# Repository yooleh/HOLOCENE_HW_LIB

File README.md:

# HOLOCENE_HW_LIB
Footprints and Symbols

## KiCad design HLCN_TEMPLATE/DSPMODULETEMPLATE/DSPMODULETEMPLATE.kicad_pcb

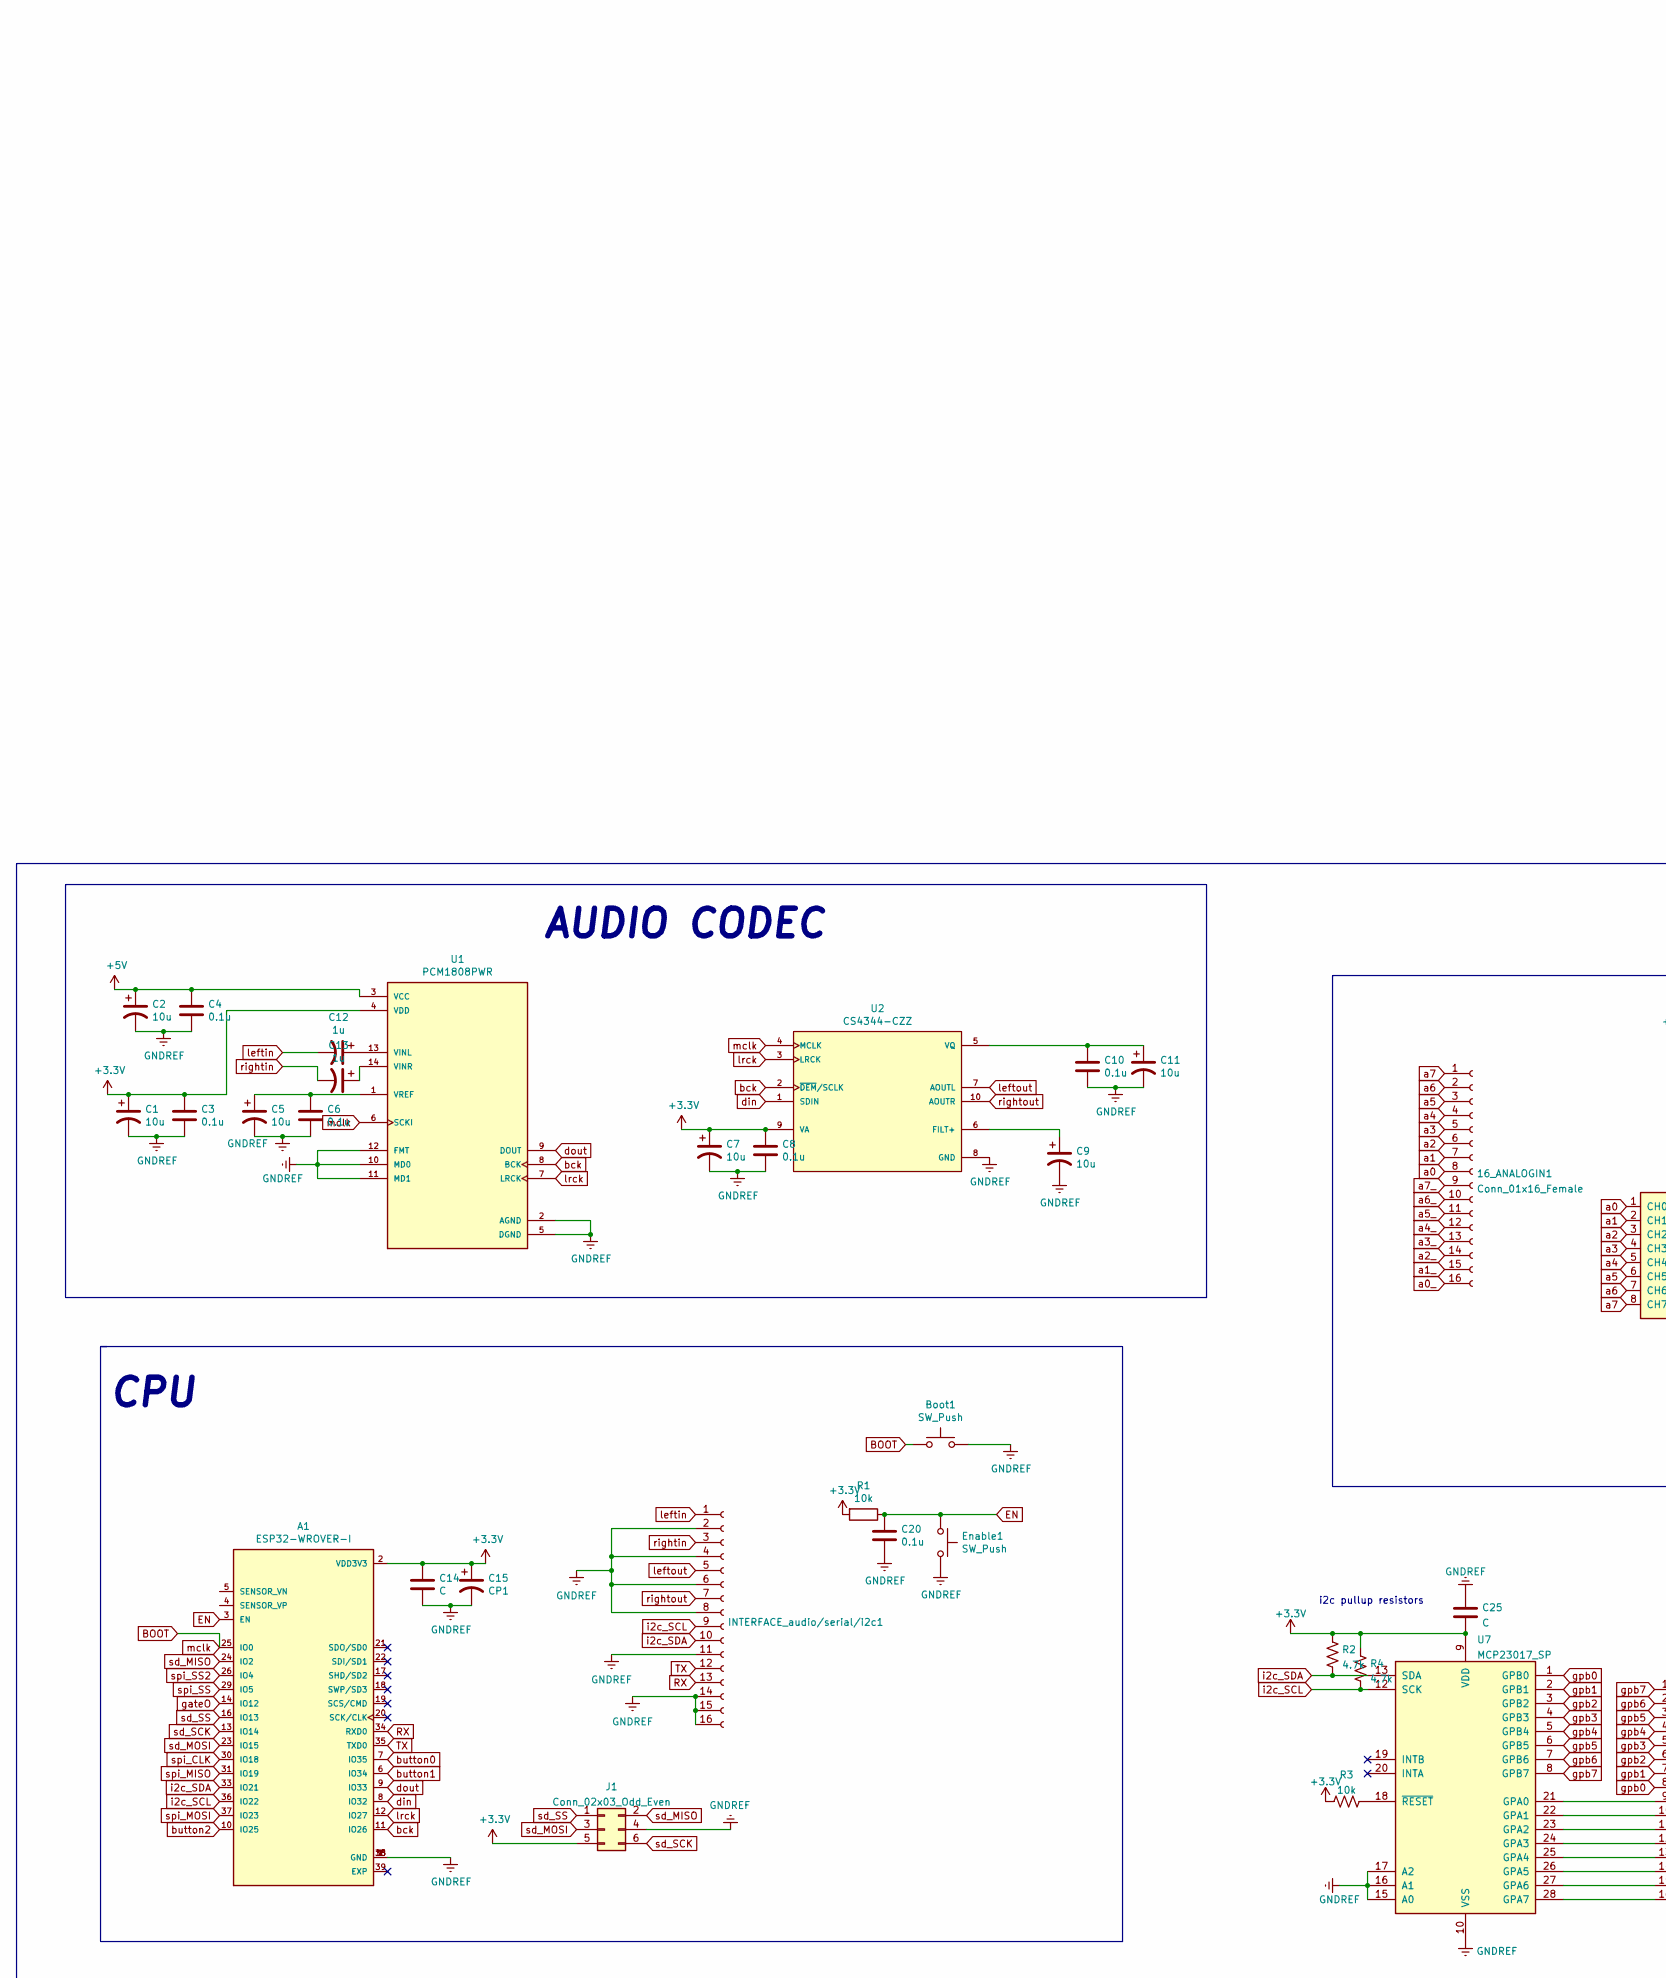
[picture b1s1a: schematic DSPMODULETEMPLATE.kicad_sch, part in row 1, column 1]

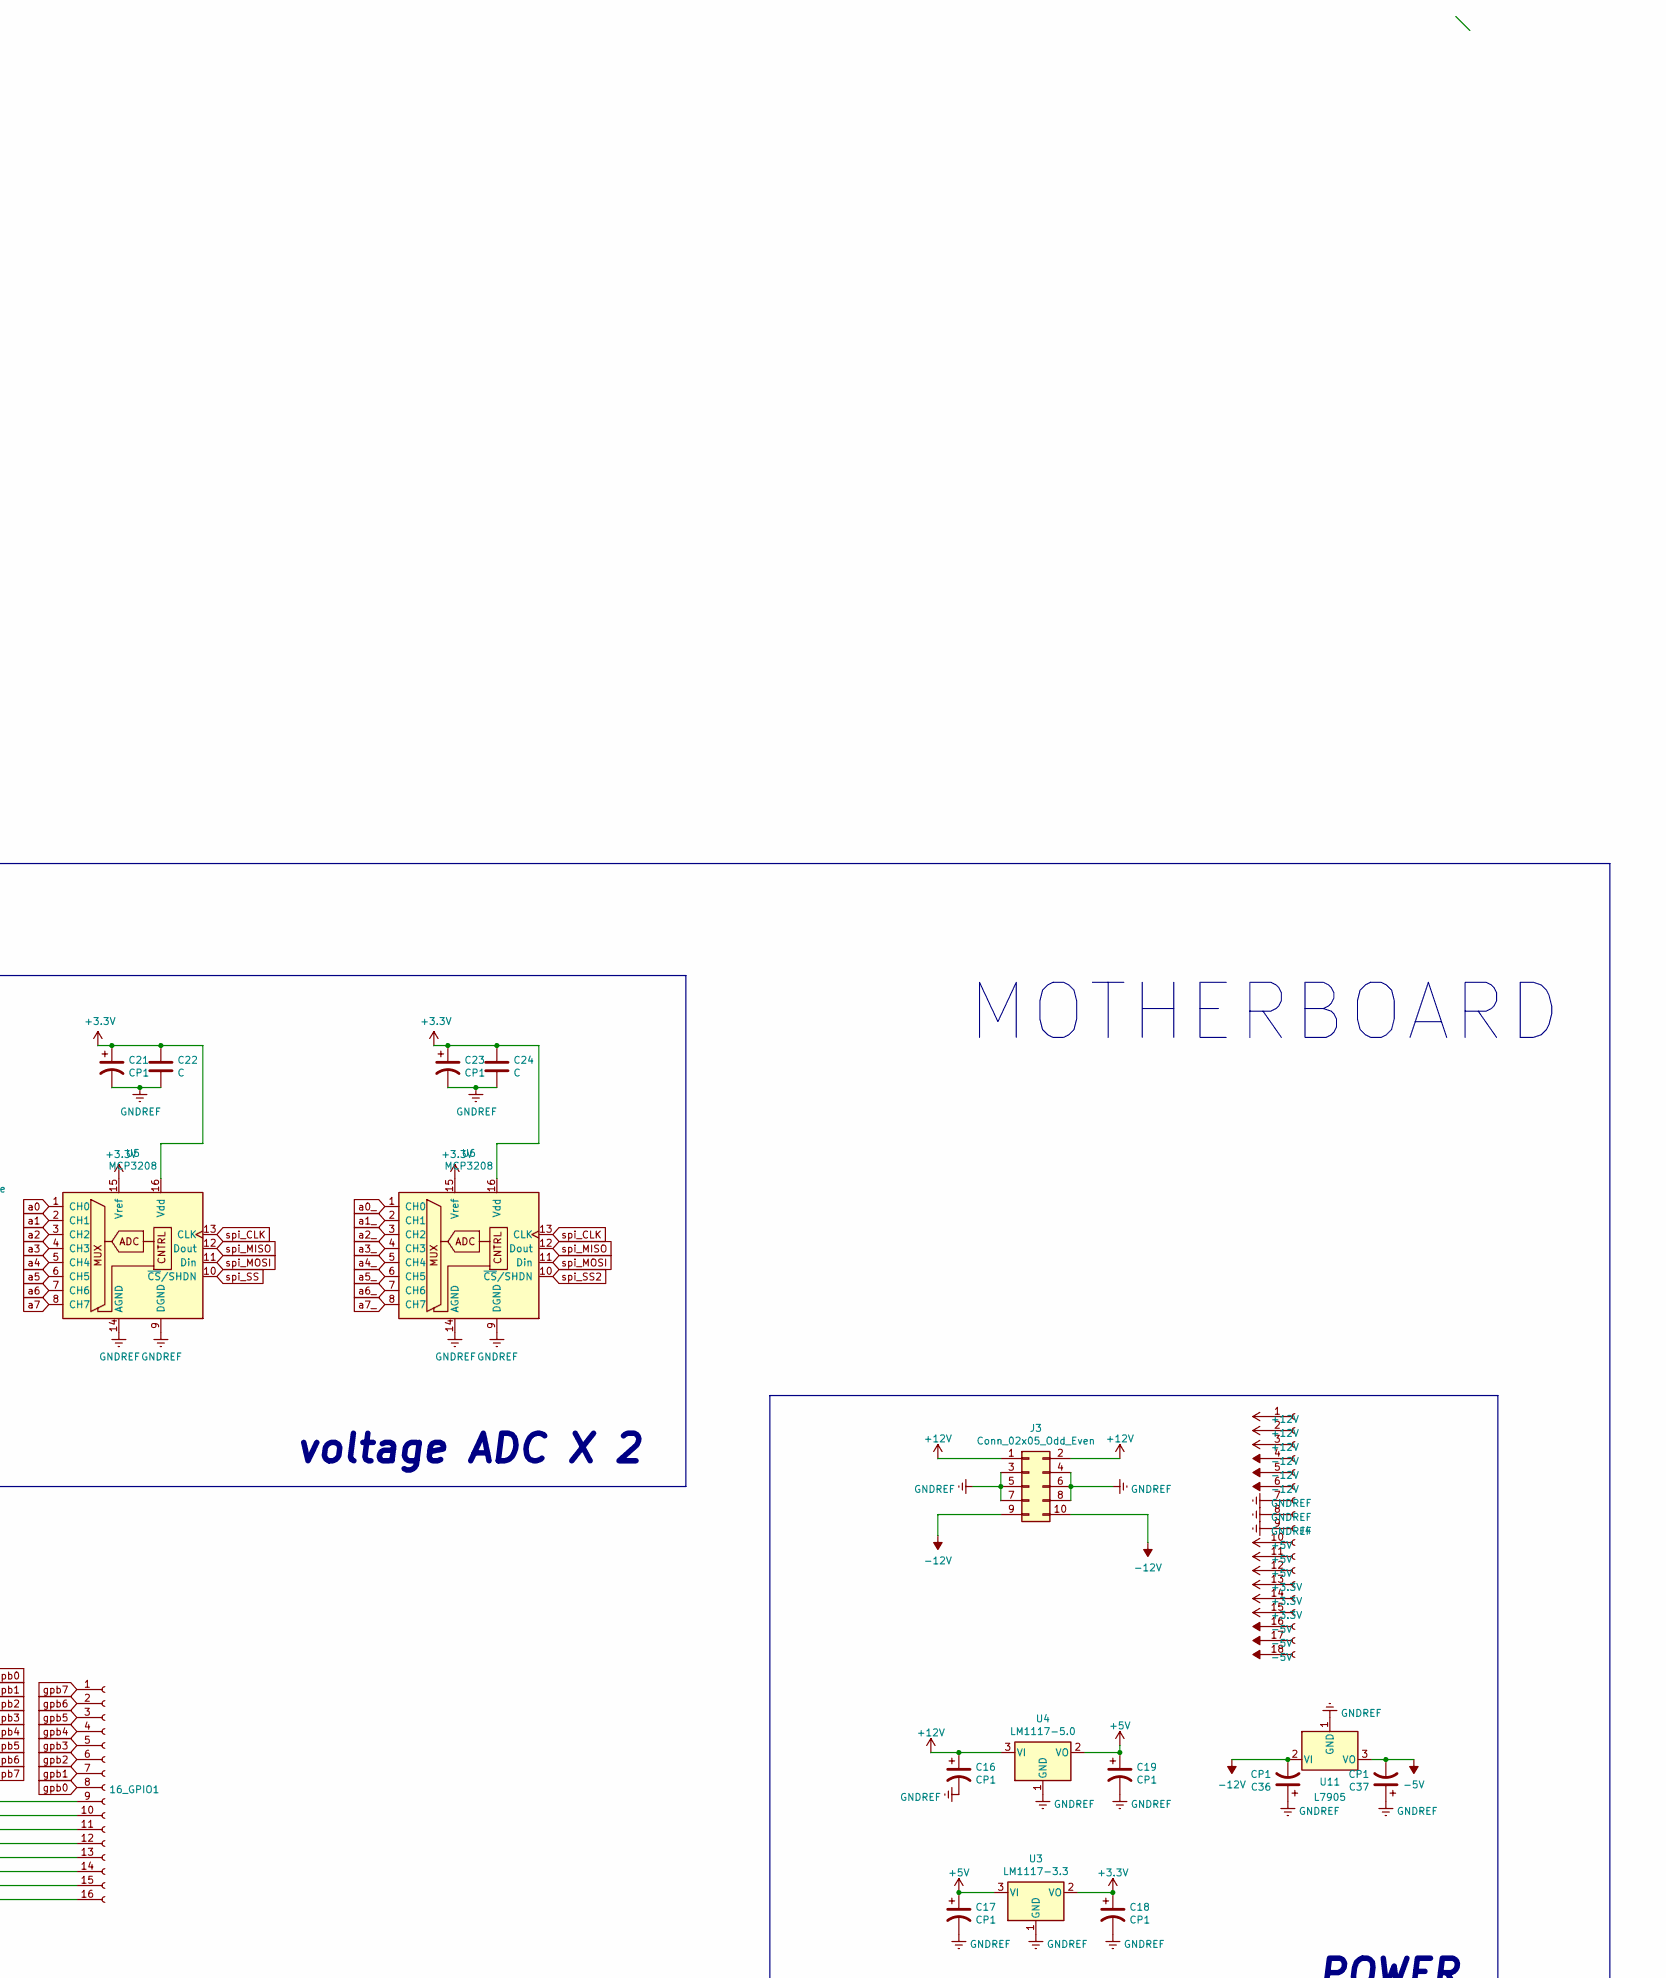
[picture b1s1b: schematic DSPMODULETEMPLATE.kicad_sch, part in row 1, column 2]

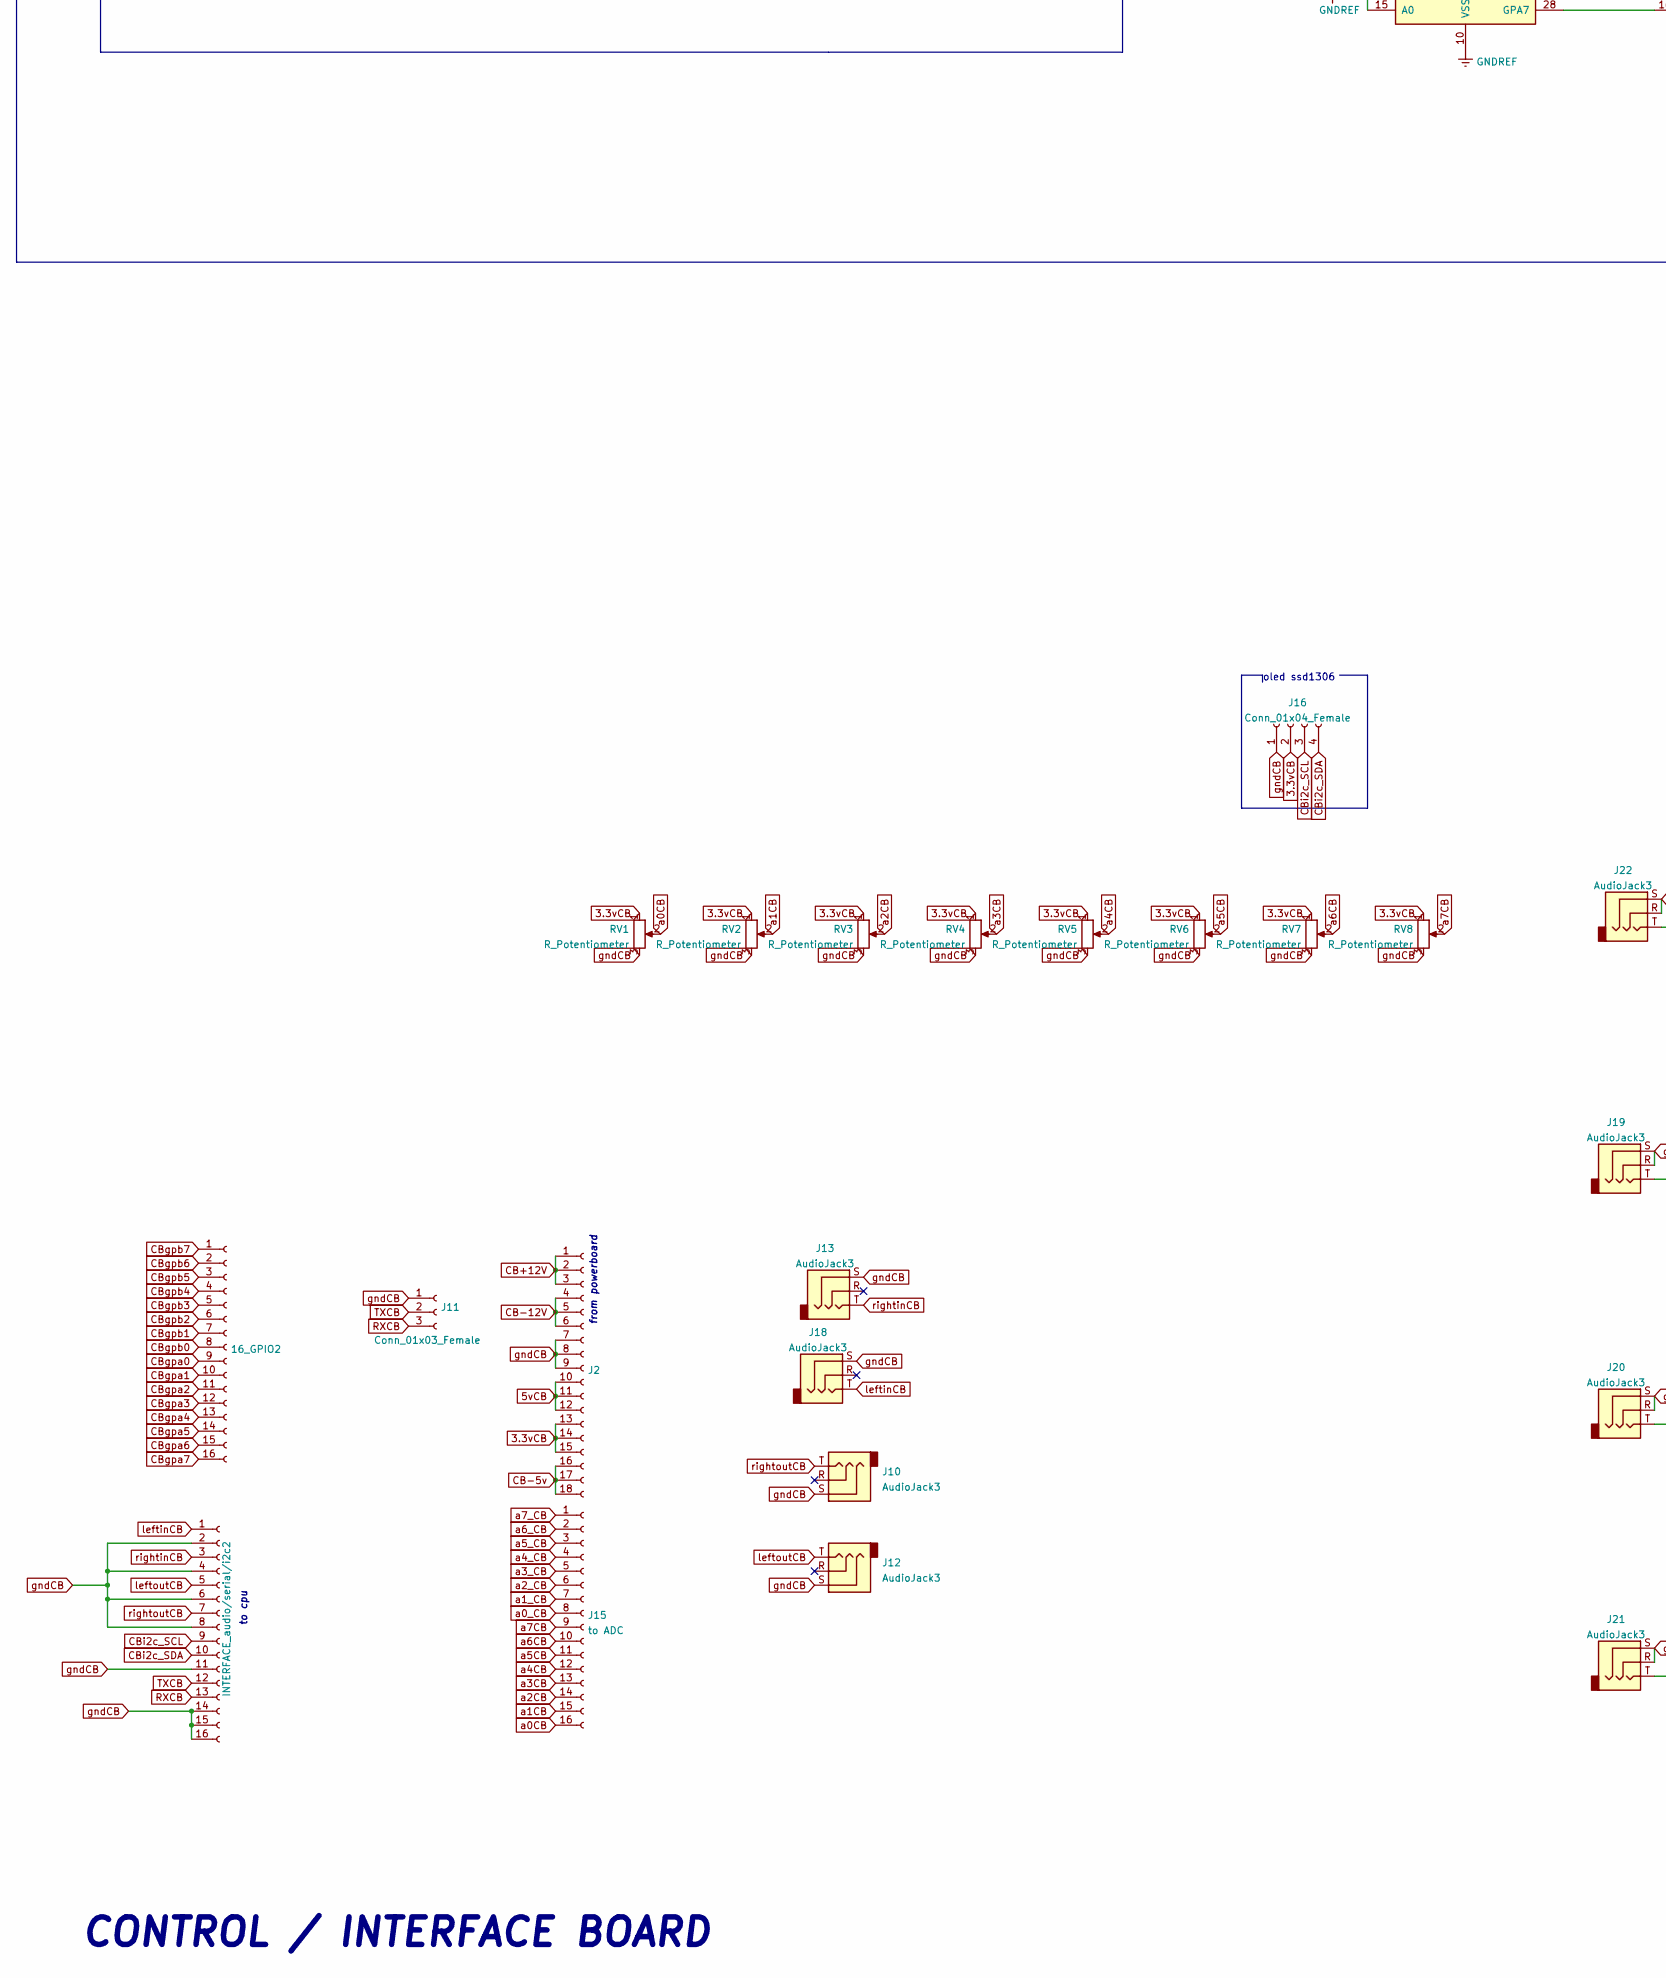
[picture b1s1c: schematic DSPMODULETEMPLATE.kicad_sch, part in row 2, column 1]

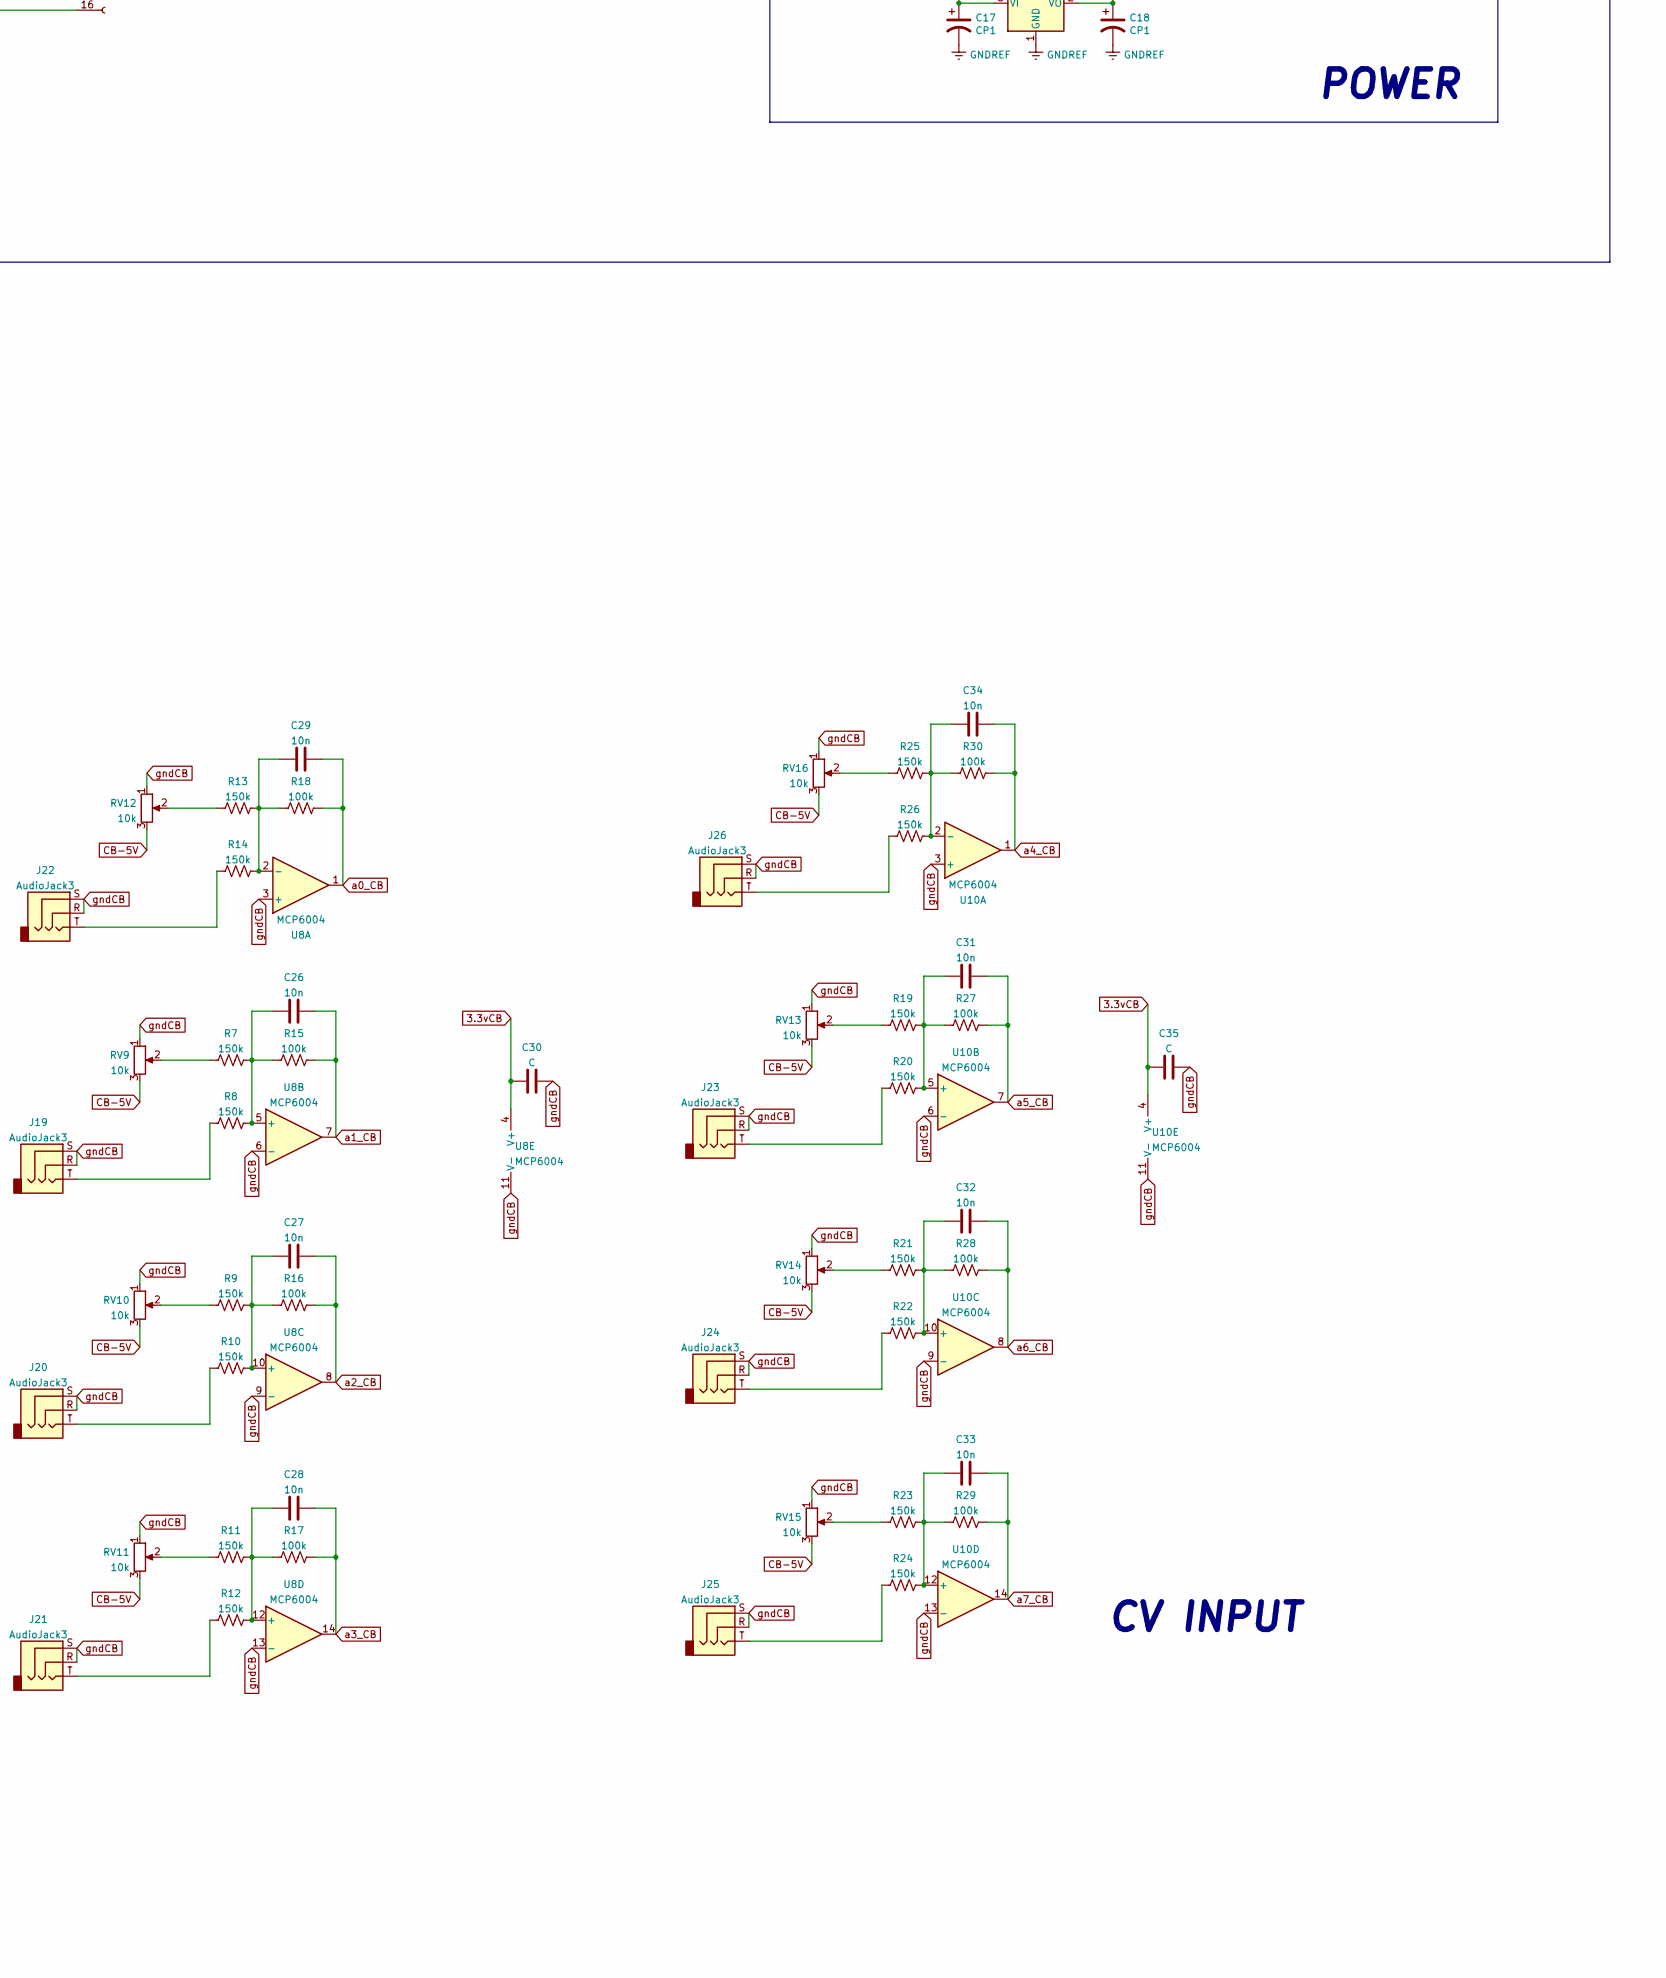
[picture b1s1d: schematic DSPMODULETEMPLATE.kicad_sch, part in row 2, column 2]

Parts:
16_ANALOGIN1, 16_GPIO1, 16_GPIO2: Conn_01x16_Female; PinSocket_1x16_P2.54mm_Vertical
A1: ESP32-WROVER-I; ESP32-WROVER
Boot1: SW_Push; SW_Push_SPST_NO_Alps_SKRK
C1, C2, C5, C7, C9, C11: 10u; CP_Elec_4x5.3
C3, C4, C6, C8, C10, C20: 0.1u; C_0805_2012Metric_Pad1.18x1.45mm_HandSolder
C12, C13: 1u; CP_Elec_4x5.3
C14, C22, C24, C25, C30, C35: C; C_0805_2012Metric_Pad1.18x1.45mm_HandSolder
C15, C16, C17, C18, C19, C21, C23, C36, C37: CP1; CP_Elec_4x5.3
C26, C27, C28, C29, C31, C32, C33, C34: 10n; C_0805_2012Metric_Pad1.18x1.45mm_HandSolder
Enable1: SW_Push; SW_Push_SPST_NO_Alps_SKRK
INTERFACE_audio/serial/i2c1, INTERFACE_audio/serial/i2c2: Conn_01x16_Female; PinHeader_1x16_P2.54mm_Vertical
J1: Conn_02x03_Odd_Even; PinHeader_2x03_P2.54mm_Vertical
J2, J4: Conn_01x18_Female; PinHeader_1x18_P2.54mm_Vertical
J3: Conn_02x05_Odd_Even; PinHeader_2x05_P2.54mm_Vertical
J10, J12, J13, J18, J19, J20, J21, J22, J23, J24, J25, J26: AudioJack3; AudioJack_3.5mm
J11: Conn_01x03_Female; PinHeader_1x03_P2.54mm_Vertical
J15: to ADC; PinSocket_1x16_P2.54mm_Vertical
J16: Conn_01x04_Female; SSD1306
R1, R3: 10k; R_0805_2012Metric_Pad1.20x1.40mm_HandSolder
R2, R4: 4.7k; R_0805_2012Metric_Pad1.20x1.40mm_HandSolder
R7, R8, R9, R10, R11, R12, R13, R14, R19, R20, R21, R22, R23, R24, R25, R26: 150k; R_0805_2012Metric_Pad1.20x1.40mm_HandSolder
R15, R16, R17, R18, R27, R28, R29, R30: 100k; R_0805_2012Metric_Pad1.20x1.40mm_HandSolder
RV1, RV2, RV3, RV4, RV6, RV8: R_Potentiometer; Potentiometer_Alps_RK09K_Single_Vertical
RV5, RV7: R_Potentiometer; Potentiometer_Bourns_PTA4543_Single_Slide
RV9, RV10, RV11, RV12, RV13, RV14, RV15, RV16: 10k; Potentiometer_Alps_RK09K_Single_Vertical
U1: PCM1808PWR; TSSOP-14_4.4x5mm_P0.65mm
U2: CS4344-CZZ; TSSOP-10_3x3mm_P0.5mm
U3: LM1117-3.3; SOT-223-3_TabPin2
U4: LM1117-5.0; SOT-223-3_TabPin2
U5, U6: MCP3208; SOIC-16_3.9x9.9mm_P1.27mm
U7: MCP23017_SP; SOIC-28W_7.5x17.9mm_P1.27mm
U8, U10: MCP6004; SOIC-14_3.9x8.7mm_P1.27mm
U11: L7905; TO-263-3_TabPin2

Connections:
3.3vCB: C30.1, C35.1, J2.13, J2.14, J2.15, J16.2, RV1.1, RV2.1, RV3.1, RV4.1, RV5.1, RV6.1, RV7.1, RV8.1, U8.4 (V+), U10.4 (V+)
5vCB: J2.10, J2.11, J2.12
+3V3: A1.2 (VDD3V3), C1.1, C3.1, C7.1, C8.1, C14.2, C15.1, C18.1, C21.1, C22.1, C23.1, C24.1, C25.2, J1.5, J4.13, J4.14, J4.15, R1.2, R2.1, R3.1, R4.1, U1.4 (VDD), U2.9 (VA), U3.2 (VO), U5.15 (Vref), U5.16 (Vdd), U6.15 (Vref), U6.16 (Vdd), U7.9 (VDD)
+5V: C2.1, C4.1, C17.1, C19.1, J4.10, J4.11, J4.12, U1.3 (VCC), U3.3 (VI), U4.2 (VO)
+12V: C16.1, J3.1, J3.2, J4.1, J4.2, J4.3, U4.3 (VI)
-5V: C37.2, J4.16, J4.17, J4.18, U11.3 (VO)
-5vCB: J2.16, J2.17, J2.18
-12V: C36.2, J3.9, J3.10, J4.4, J4.5, J4.6, U11.2 (VI)
BOOT: A1.25 (IO0), Boot1.1, U1.6 (SCKI), U2.4 (MCLK)
CB+12V: J2.1, J2.2, J2.3
CB-5V: RV9.3, RV10.3, RV11.3, RV12.3, RV13.3, RV14.3, RV15.3, RV16.3
CB-12V: J2.4, J2.5, J2.6
CBgpa0: 16_GPIO2.9
CBgpa1: 16_GPIO2.10
CBgpa2: 16_GPIO2.11
CBgpa3: 16_GPIO2.12
CBgpa4: 16_GPIO2.13
CBgpa5: 16_GPIO2.14
CBgpa6: 16_GPIO2.15
CBgpa7: 16_GPIO2.16
CBgpb0: 16_GPIO2.8
CBgpb1: 16_GPIO2.7
CBgpb2: 16_GPIO2.6
CBgpb3: 16_GPIO2.5
CBgpb4: 16_GPIO2.4
CBgpb5: 16_GPIO2.3
CBgpb6: 16_GPIO2.2
CBgpb7: 16_GPIO2.1
CBi2c_SCL: INTERFACE_audio/serial/i2c2.9, J16.3
CBi2c_SDA: INTERFACE_audio/serial/i2c2.10, J16.4
EN: A1.3 (EN), C20.1, Enable1.1, R1.1
GNDREF: A1.1 (GND), A1.15 (GND), A1.38 (GND), Boot1.2, C1.2, C2.2, C3.2, C4.2, C5.2, C6.2, C7.2, C8.2, C9.2, C10.2, C11.2, C14.1, C15.2, C16.2, C17.2, C18.2, C19.2, C20.2, C21.2, C22.2, C23.2, C24.2, C25.1, C36.1, C37.1, Enable1.2, INTERFACE_audio/serial/i2c1.2, INTERFACE_audio/serial/i2c1.4, INTERFACE_audio/serial/i2c1.6, INTERFACE_audio/serial/i2c1.8, INTERFACE_audio/serial/i2c1.11, INTERFACE_audio/serial/i2c1.14, INTERFACE_audio/serial/i2c1.15, INTERFACE_audio/serial/i2c1.16, J1.4, J3.3, J3.4, J3.5, J3.6, J3.7, J3.8, J4.7, J4.8, J4.9, U1.2 (AGND), U1.5 (DGND), U1.10 (MD0), U1.11 (MD1), U1.12 (FMT), U2.8 (GND), U3.1 (GND), U4.1 (GND), U5.9 (DGND), U5.14 (AGND), U6.9 (DGND), U6.14 (AGND), U7.10 (VSS), U7.15 (A0), U7.16 (A1), U7.17 (A2), U11.1 (GND)
unnamed: 16_GPIO1.9, U7.21 (GPA0)
unnamed: 16_GPIO1.10, U7.22 (GPA1)
unnamed: 16_GPIO1.11, U7.23 (GPA2)
unnamed: 16_GPIO1.12, U7.24 (GPA3)
unnamed: 16_GPIO1.13, U7.25 (GPA4)
unnamed: 16_GPIO1.14, U7.26 (GPA5)
unnamed: 16_GPIO1.15, U7.27 (GPA6)
unnamed: 16_GPIO1.16, U7.28 (GPA7)
unnamed: C5.1, C6.1, U1.1 (VREF)
unnamed: C9.1, U2.6 (FILT+)
unnamed: C10.1, C11.1, U2.5 (VQ)
unnamed: C12.1, U1.13 (VINL)
unnamed: C13.1, U1.14 (VINR)
unnamed: C26.1, R7.2, R8.2, R15.1, U8.5 (+)
unnamed: C27.1, R9.2, R10.2, R16.1, U8.10 (+)
unnamed: C28.1, R11.2, R12.2, R17.1, U8.12 (+)
unnamed: C29.1, R13.2, R14.2, R18.1, U8.2 (-)
unnamed: C31.1, R19.2, R20.2, R27.1, U10.5 (+)
unnamed: C32.1, R21.2, R22.2, R28.1, U10.10 (+)
unnamed: C33.1, R23.2, R24.2, R29.1, U10.12 (+)
unnamed: C34.1, R25.2, R26.2, R30.1, U10.2 (-)
unnamed: J19.T, R8.1
unnamed: J20.T, R10.1
unnamed: J21.T, R12.1
unnamed: J22.T, R14.1
unnamed: J23.T, R20.1
unnamed: J24.T, R22.1
unnamed: J25.T, R24.1
unnamed: J26.T, R26.1
unnamed: R3.2, U7.18 (~RESET)
unnamed: R7.1, RV9.2
unnamed: R9.1, RV10.2
unnamed: R11.1, RV11.2
unnamed: R13.1, RV12.2
unnamed: R19.1, RV13.2
unnamed: R21.1, RV14.2
unnamed: R23.1, RV15.2
unnamed: R25.1, RV16.2
RX: A1.34 (RXD0), INTERFACE_audio/serial/i2c1.13
RXCB: INTERFACE_audio/serial/i2c2.13, J11.3
TX: A1.35 (TXD0), INTERFACE_audio/serial/i2c1.12
TXCB: INTERFACE_audio/serial/i2c2.12, J11.2
a0: 16_ANALOGIN1.8, U5.1 (CH0)
a0CB: J15.16, RV1.2
a0_: 16_ANALOGIN1.16, U6.1 (CH0)
a0_CB: C29.2, J15.8, R18.2, U8.1
a1: 16_ANALOGIN1.7, U5.2 (CH1)
a1CB: J15.15, RV2.2
a1_: 16_ANALOGIN1.15, U6.2 (CH1)
a1_CB: C26.2, J15.7, R15.2, U8.7
a2: 16_ANALOGIN1.6, U5.3 (CH2)
a2CB: J15.14, RV3.2
a2_: 16_ANALOGIN1.14, U6.3 (CH2)
a2_CB: C27.2, J15.6, R16.2, U8.8
a3: 16_ANALOGIN1.5, U5.4 (CH3)
a3CB: J15.13, RV4.2
a3_: 16_ANALOGIN1.13, U6.4 (CH3)
a3_CB: C28.2, J15.5, R17.2, U8.14
a4: 16_ANALOGIN1.4, U5.5 (CH4)
a4CB: J15.12, RV5.2
a4_: 16_ANALOGIN1.12, U6.5 (CH4)
a4_CB: C34.2, J15.4, R30.2, U10.1
a5: 16_ANALOGIN1.3, U5.6 (CH5)
a5CB: J15.11, RV6.2
a5_: 16_ANALOGIN1.11, U6.6 (CH5)
a5_CB: C31.2, J15.3, R27.2, U10.7
a6: 16_ANALOGIN1.2, U5.7 (CH6)
a6CB: J15.10, RV7.2
a6_: 16_ANALOGIN1.10, U6.7 (CH6)
a6_CB: C32.2, J15.2, R28.2, U10.8
a7: 16_ANALOGIN1.1, U5.8 (CH7)
a7CB: J15.9, RV8.2
a7_: 16_ANALOGIN1.9, U6.8 (CH7)
a7_CB: C33.2, J15.1, R29.2, U10.14
bck: A1.11 (IO26), U1.8 (BCK), U2.2 (~DEM/SCLK)
button0: A1.7 (IO35)
button1: A1.6 (IO34)
button2: A1.10 (IO25)
din: A1.8 (IO32), U2.1 (SDIN)
dout: A1.9 (IO33), U1.9 (DOUT)
gateO: A1.14 (IO12)
gndCB: C30.2, C35.2, INTERFACE_audio/serial/i2c2.2, INTERFACE_audio/serial/i2c2.4, INTERFACE_audio/serial/i2c2.6, INTERFACE_audio/serial/i2c2.8, INTERFACE_audio/serial/i2c2.11, INTERFACE_audio/serial/i2c2.14, INTERFACE_audio/serial/i2c2.15, INTERFACE_audio/serial/i2c2.16, J2.7, J2.8, J2.9, J10.S, J11.1, J12.S, J13.S, J16.1, J18.S, J19.R, J19.S, J20.R, J20.S, J21.R, J21.S, J22.R, J22.S, J23.R, J23.S, J24.R, J24.S, J25.R, J25.S, J26.R, J26.S, RV1.3, RV2.3, RV3.3, RV4.3, RV5.3, RV6.3, RV7.3, RV8.3, RV9.1, RV10.1, RV11.1, RV12.1, RV13.1, RV14.1, RV15.1, RV16.1, U8.3 (+), U8.6 (-), U8.9 (-), U8.11 (V-), U8.13 (-), U10.3 (+), U10.6 (-), U10.9 (-), U10.11 (V-), U10.13 (-)
gpb0: 16_GPIO1.8, U7.1 (GPB0)
gpb1: 16_GPIO1.7, U7.2 (GPB1)
gpb2: 16_GPIO1.6, U7.3 (GPB2)
gpb3: 16_GPIO1.5, U7.4 (GPB3)
gpb4: 16_GPIO1.4, U7.5 (GPB4)
gpb5: 16_GPIO1.3, U7.6 (GPB5)
gpb6: 16_GPIO1.2, U7.7 (GPB6)
gpb7: 16_GPIO1.1, U7.8 (GPB7)
i2c_SCL: A1.36 (IO22), INTERFACE_audio/serial/i2c1.9, R4.2, U7.12 (SCK)
i2c_SDA: A1.33 (IO21), INTERFACE_audio/serial/i2c1.10, R2.2, U7.13 (SDA)
leftin: C12.2, INTERFACE_audio/serial/i2c1.1
leftinCB: INTERFACE_audio/serial/i2c2.1, J18.T
leftout: INTERFACE_audio/serial/i2c1.5, U2.7 (AOUTL)
leftoutCB: INTERFACE_audio/serial/i2c2.5, J12.T
lrck: A1.12 (IO27), U1.7 (LRCK), U2.3 (LRCK)
rightin: C13.2, INTERFACE_audio/serial/i2c1.3
rightinCB: INTERFACE_audio/serial/i2c2.3, J13.T
rightout: INTERFACE_audio/serial/i2c1.7, U2.10 (AOUTR)
rightoutCB: INTERFACE_audio/serial/i2c2.7, J10.T
sd_MISO: A1.24 (IO2), J1.2
sd_MOSI: A1.23 (IO15), J1.3
sd_SCK: A1.13 (IO14), J1.6
sd_SS: A1.16 (IO13), J1.1
spi_CLK: A1.30 (IO18), U5.13 (CLK), U6.13 (CLK)
spi_MISO: A1.31 (IO19), U5.12 (Dout), U6.12 (Dout)
spi_MOSI: A1.37 (IO23), U5.11 (Din), U6.11 (Din)
spi_SS: A1.29 (IO5), U5.10 (~CS/SHDN)
spi_SS2: A1.26 (IO4), U6.10 (~CS/SHDN)

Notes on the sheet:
POWER
i2c pullup resistors
MOTHERBOARD
to cpu
CPU
AUDIO CODEC
oled ssd1306
CONTROL / INTERFACE BOARD
CV INPUT
voltage ADC X 2
from powerboard

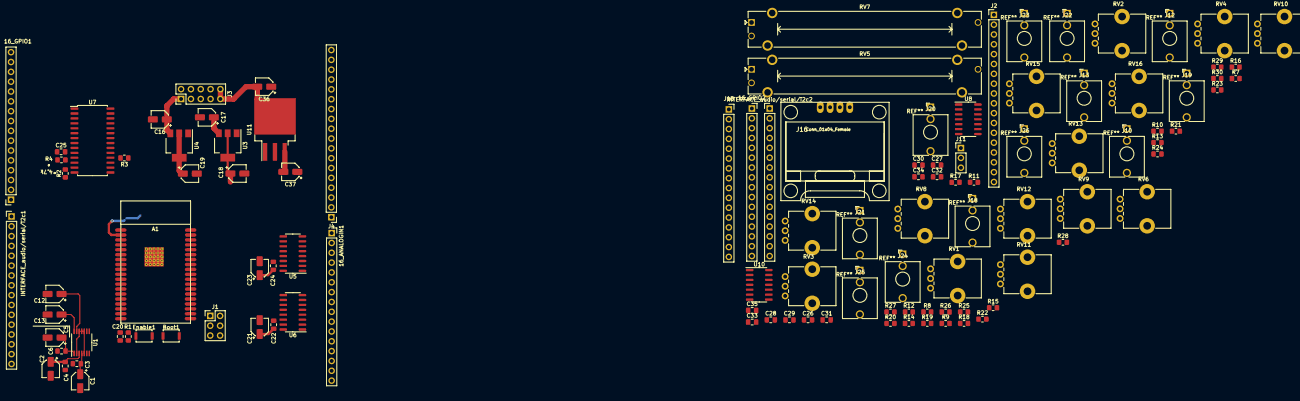
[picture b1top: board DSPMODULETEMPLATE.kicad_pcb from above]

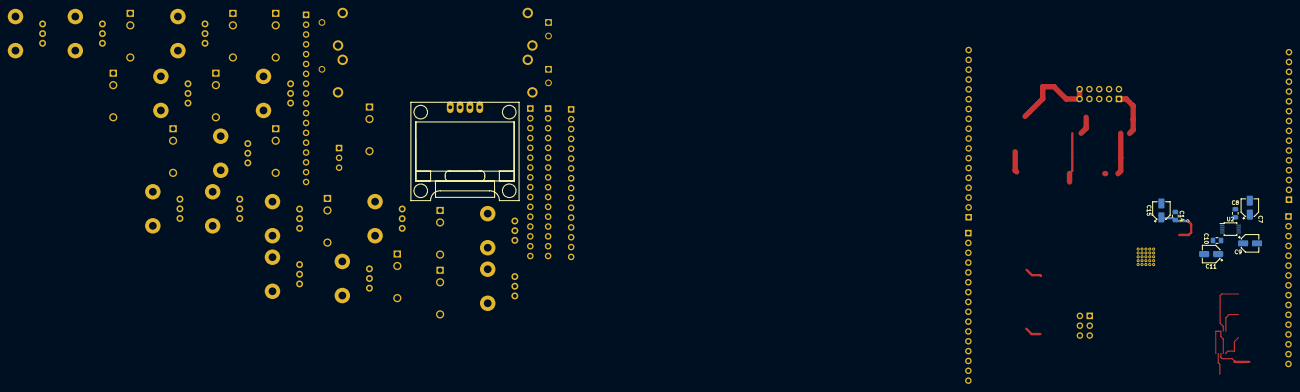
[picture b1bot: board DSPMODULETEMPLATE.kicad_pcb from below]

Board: 2 copper layers, 118 parts (8 on the bottom side), 122 nets.
